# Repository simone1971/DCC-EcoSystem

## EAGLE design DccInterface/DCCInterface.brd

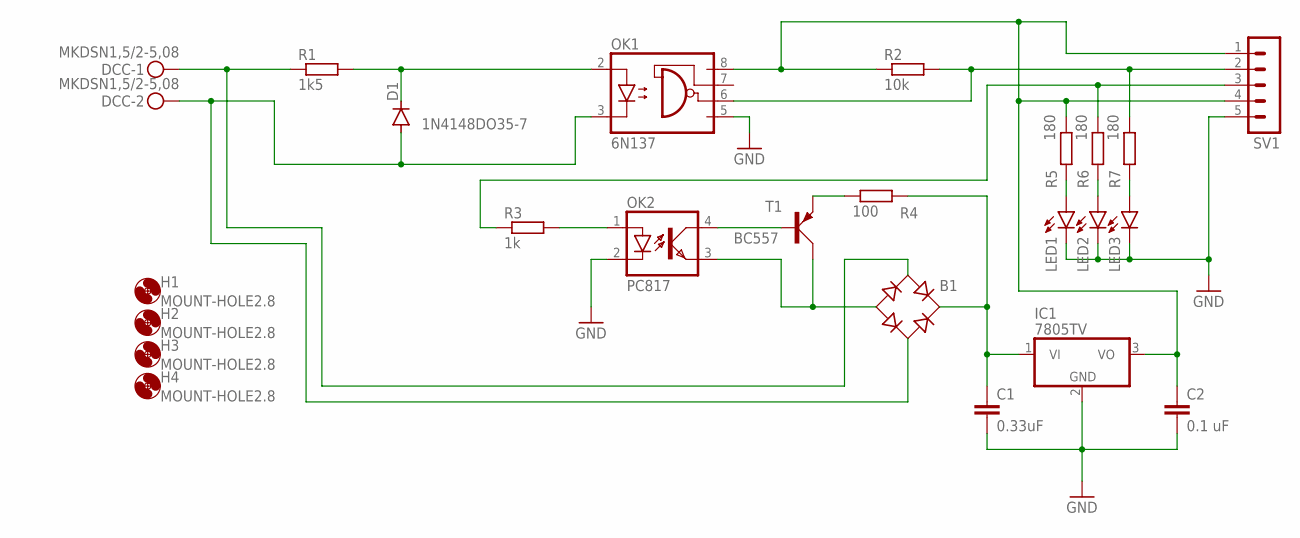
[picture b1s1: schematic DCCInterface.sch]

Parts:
B1: RB1A
C1: 0.33uF; C025-025X050
C2: 0.1 uF; C025-025X050
D1: 1N4148DO35-7; DO35-7
DCC: MKDSN1,5/2-5,08
H1, H2, H3, H4: MOUNT-HOLE2.8; 2,8
IC1: 7805TV; TO220V
LED1, LED2, LED3: LED3MM
OK1: 6N137; DIL08
OK2: PC817; DIL04
R1: 1k5; 0204/7
R2: 10k; 0204/7
R3: 1k; 0204/7
R4: 100; 0204/7
R5, R6, R7: 180; 0204/7
SV1: MA05-1
T1: BC557; SOT54A

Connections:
GND: C1.2, C2.2, IC1.2 (GND), LED1.K (C), LED2.K (C), LED3.K (C), OK1.5 (GND), OK2.2 (C), SV1.5
unnamed: LED1.A, R5.1
unnamed: C2.1, IC1.3 (VO), OK1.8 (VCC), R2.1, R5.2, SV1.1, SV1.4
unnamed: D1.C, OK1.2 (A), R1.2
unnamed: LED2.A, R6.1
unnamed: OK1.6 (VO), R2.2, R7.2, SV1.2
unnamed: B1.AC1, DCC.1, R1.1
unnamed: OK2.1 (A), R3.2
unnamed: OK2.4 (COL), T1.B
unnamed: B1.+, C1.1, IC1.1 (VI), R4.2
unnamed: B1.-, OK2.3 (EMIT), T1.C
unnamed: R4.1, T1.E
unnamed: R3.1, R6.2, SV1.3
unnamed: B1.AC2, D1.A, DCC.2, OK1.3 (C)
unnamed: LED3.A, R7.1

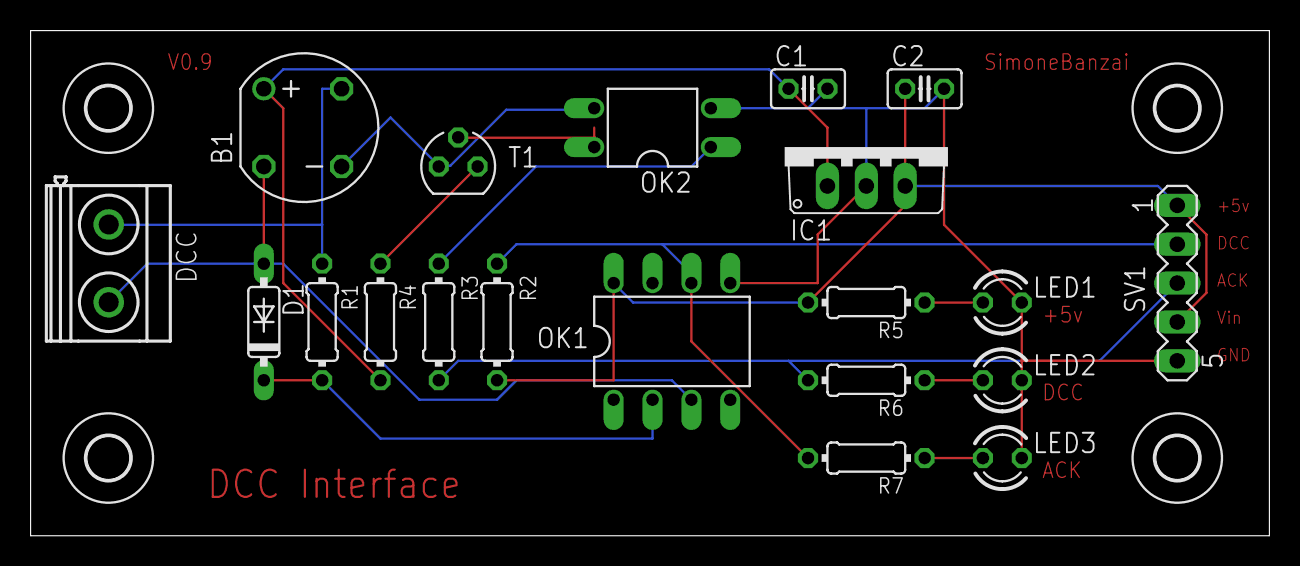
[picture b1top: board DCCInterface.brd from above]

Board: 2 copper layers, 81.0 x 33.0 mm, 24 parts (0 on the bottom side), 15 nets.

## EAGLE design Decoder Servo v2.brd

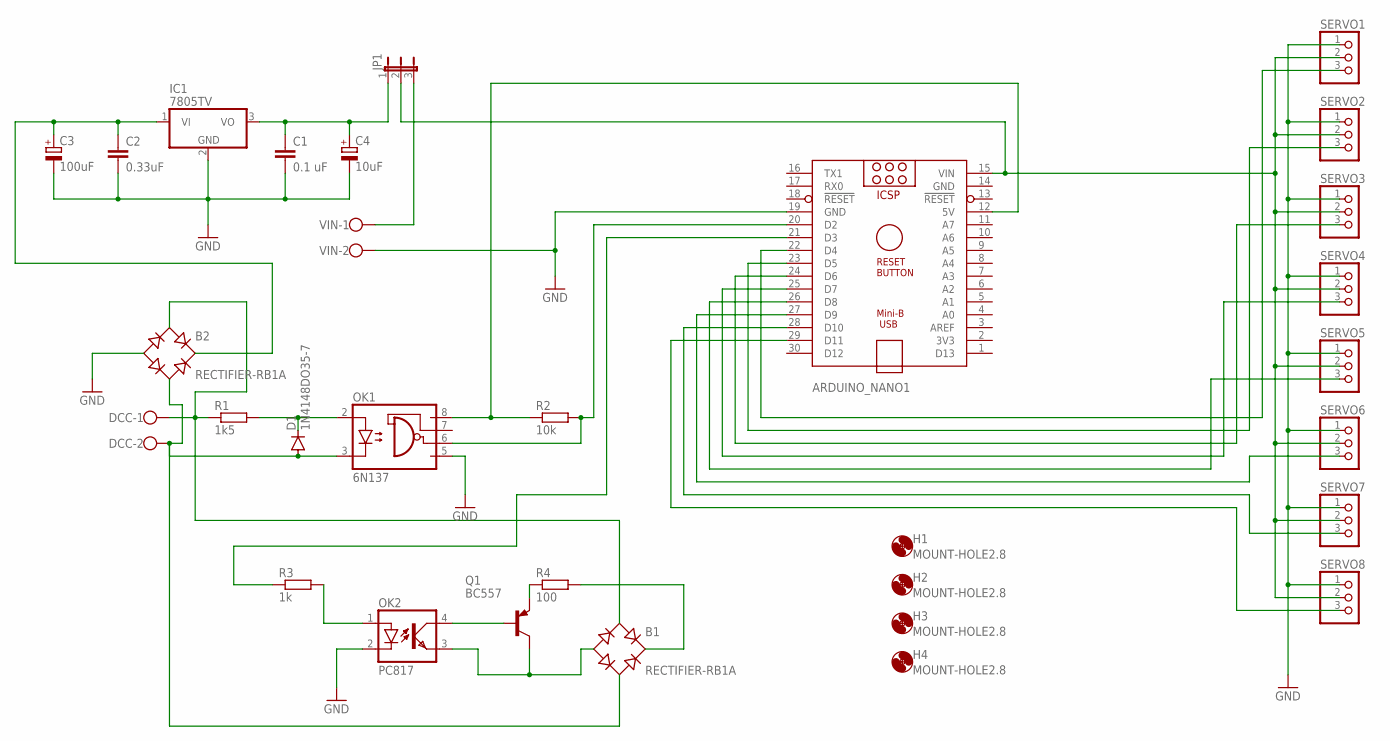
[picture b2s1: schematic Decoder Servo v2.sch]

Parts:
ARDUINO_NANO1: ARDUINO_NANO
B1, B2: RECTIFIER-RB1A; RB1A
C1: 0.1 uF; C025-024X044
C2: 0.33uF; C025-024X044
C3: 100uF; TAP5-50
C4: 10uF; TAP5-50
D1: 1N4148DO35-7; DO35-7
DCC: W237-102
H1, H2, H3, H4: MOUNT-HOLE2.8; 2,8
IC1: 7805TV; TO220V
JP1: JP2E; JP2
OK1: 6N137; DIL08
OK2: PC817; DIL04
Q1: BC557; TO92
R1: 1k5; 0207/10
R2: 10k; 0207/10
R3: 1k; 0207/10
R4: 100; 0207/10
SERVO1, SERVO2, SERVO3, SERVO4, SERVO5, SERVO6, SERVO7, SERVO8: PINHD-1X3; 1X03
VIN: W237-102

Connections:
GND: ARDUINO_NANO1.14 (GND), ARDUINO_NANO1.19 (GND), B2.-, C1.2, C2.2, C3.-, C4.-, IC1.2 (GND), OK1.5 (GND), OK2.2 (C), SERVO1.1, SERVO2.1, SERVO3.1, SERVO4.1, SERVO5.1, SERVO6.1, SERVO7.1, SERVO8.1, VIN.2
unnamed: D1.C, OK1.2 (A), R1.2
unnamed: B1.AC2, B2.AC2, D1.A, DCC.2, OK1.3 (C)
unnamed: ARDUINO_NANO1.12 (5V), OK1.8 (VCC), R2.1
unnamed: ARDUINO_NANO1.20 (D2), OK1.6 (VO), R2.2
unnamed: B1.AC1, B2.AC1, DCC.1, R1.1
unnamed: OK2.4 (COL), Q1.2 (B)
unnamed: ARDUINO_NANO1.21 (D3), R3.1
unnamed: OK2.1 (A), R3.2
unnamed: B1.-, OK2.3 (EMIT), Q1.3 (C)
unnamed: Q1.1 (E), R4.1
unnamed: B1.+, R4.2
unnamed: ARDUINO_NANO1.22 (D4), SERVO1.3
unnamed: B2.+, C2.1, C3.+, IC1.1 (VI)
unnamed: ARDUINO_NANO1.15 (VIN), JP1.2, SERVO1.2, SERVO2.2, SERVO3.2, SERVO4.2, SERVO5.2, SERVO6.2, SERVO7.2, SERVO8.2
unnamed: ARDUINO_NANO1.23 (D5), SERVO2.3
unnamed: ARDUINO_NANO1.24 (D6), SERVO3.3
unnamed: ARDUINO_NANO1.25 (D7), SERVO4.3
unnamed: ARDUINO_NANO1.26 (D8), SERVO5.3
unnamed: ARDUINO_NANO1.27 (D9), SERVO6.3
unnamed: ARDUINO_NANO1.28 (D10), SERVO7.3
unnamed: ARDUINO_NANO1.29 (D11), SERVO8.3
unnamed: C1.1, C4.+, IC1.3 (VO), JP1.1
unnamed: JP1.3, VIN.1

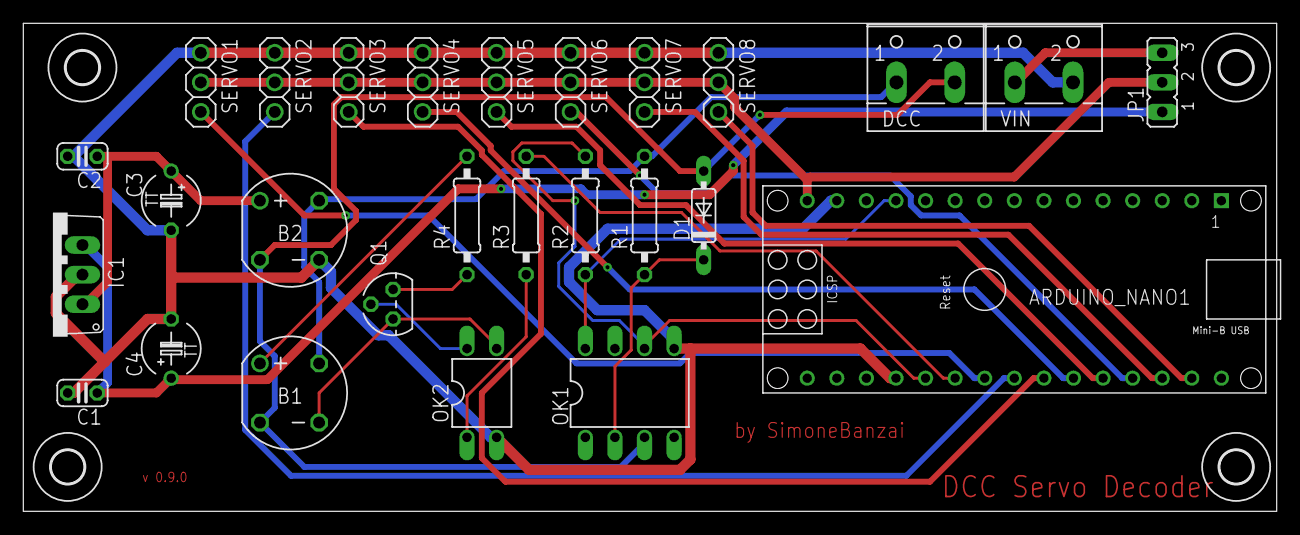
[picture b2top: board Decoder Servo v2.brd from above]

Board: 2 copper layers, 107.6 x 41.9 mm, 31 parts (0 on the bottom side), 24 nets.

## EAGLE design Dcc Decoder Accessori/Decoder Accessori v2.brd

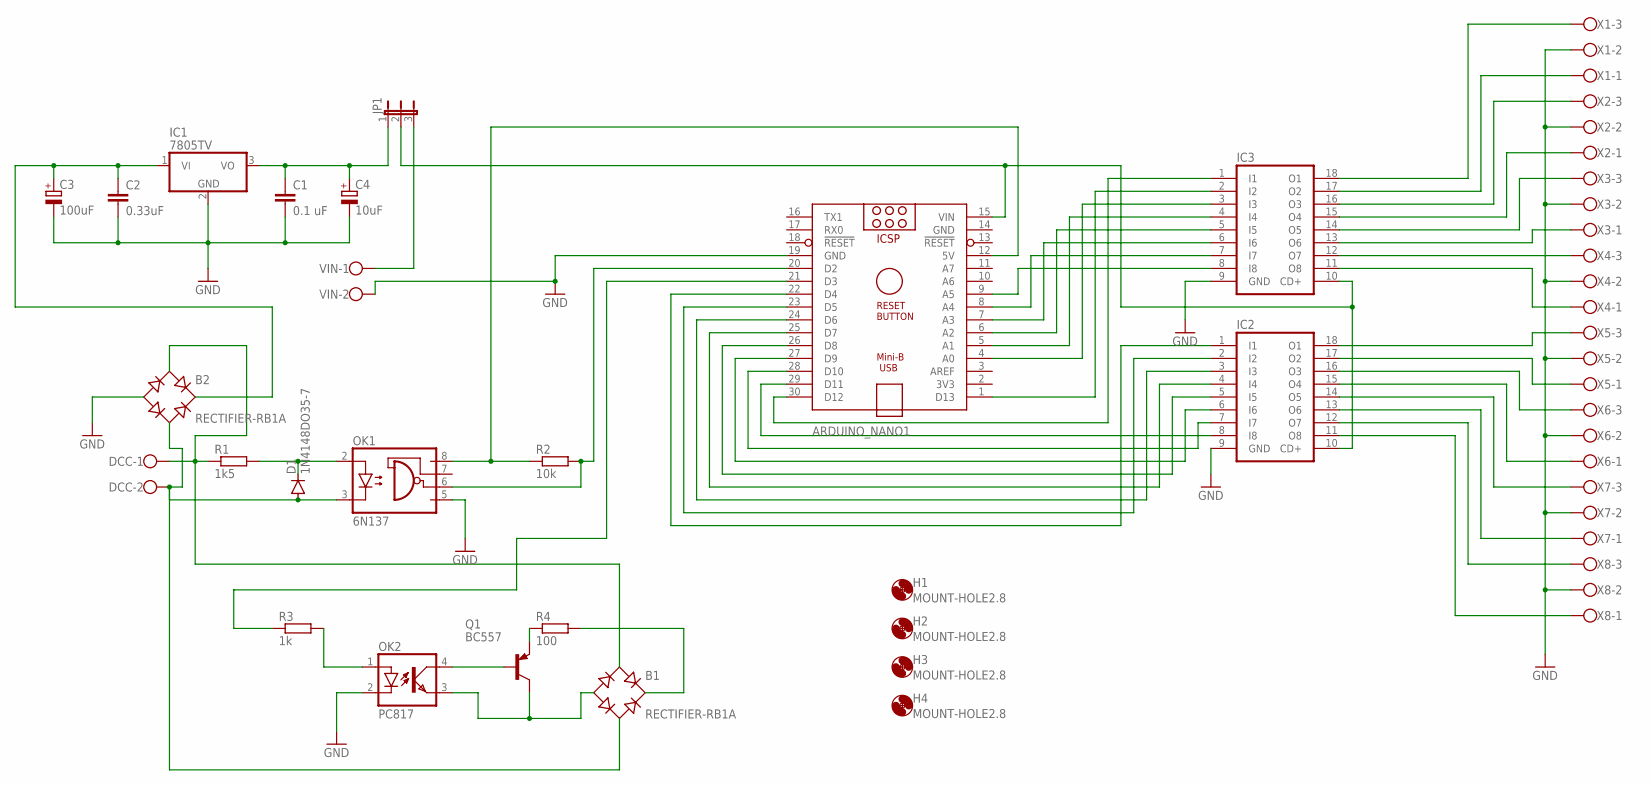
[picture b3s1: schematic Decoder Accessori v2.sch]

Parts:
ARDUINO_NANO1: ARDUINO_NANO
B1, B2: RECTIFIER-RB1A; RB1A
C1: 0.1 uF; C025-024X044
C2: 0.33uF; C025-024X044
C3: 100uF; TAP5-50
C4: 10uF; TAP5-50
D1: 1N4148DO35-7; DO35-7
DCC: W237-102
H1, H2, H3, H4: MOUNT-HOLE2.8; 2,8
IC1: 7805TV; TO220V
IC2, IC3: ULN2803A; DIL18
JP1: JP2E; JP2
OK1: 6N137; DIL08
OK2: PC817; DIL04
Q1: BC557; TO92
R1: 1k5; 0207/10
R2: 10k; 0207/10
R3: 1k; 0207/10
R4: 100; 0207/10
VIN: W237-102
X1, X2, X3, X4, X5, X6, X7, X8: W237-103

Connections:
GND: ARDUINO_NANO1.14 (GND), ARDUINO_NANO1.19 (GND), B2.-, C1.2, C2.2, C3.-, C4.-, IC1.2 (GND), IC2.9 (GND), IC3.9 (GND), OK1.5 (GND), OK2.2 (C), VIN.2, X1.2, X2.2, X3.2, X4.2, X5.2, X6.2, X7.2, X8.2
unnamed: D1.C, OK1.2 (A), R1.2
unnamed: B1.AC2, B2.AC2, D1.A, DCC.2, OK1.3 (C)
unnamed: ARDUINO_NANO1.12 (5V), OK1.8 (VCC), R2.1
unnamed: ARDUINO_NANO1.20 (D2), OK1.6 (VO), R2.2
unnamed: B1.AC1, B2.AC1, DCC.1, R1.1
unnamed: OK2.4 (COL), Q1.2 (B)
unnamed: ARDUINO_NANO1.21 (D3), R3.1
unnamed: OK2.1 (A), R3.2
unnamed: B1.-, OK2.3 (EMIT), Q1.3 (C)
unnamed: Q1.1 (E), R4.1
unnamed: B1.+, R4.2
unnamed: ARDUINO_NANO1.29 (D11), IC2.8 (I8)
unnamed: ARDUINO_NANO1.28 (D10), IC2.7 (I7)
unnamed: B2.+, C2.1, C3.+, IC1.1 (VI)
unnamed: ARDUINO_NANO1.15 (VIN), IC2.10 (CD+), IC3.10 (CD+), JP1.2
unnamed: ARDUINO_NANO1.27 (D9), IC2.6 (I6)
unnamed: ARDUINO_NANO1.26 (D8), IC2.5 (I5)
unnamed: ARDUINO_NANO1.30 (D12), IC3.1 (I1)
unnamed: ARDUINO_NANO1.25 (D7), IC2.4 (I4)
unnamed: ARDUINO_NANO1.24 (D6), IC2.3 (I3)
unnamed: ARDUINO_NANO1.23 (D5), IC2.2 (I2)
unnamed: ARDUINO_NANO1.22 (D4), IC2.1 (I1)
unnamed: ARDUINO_NANO1.1 (D13), IC3.2 (I2)
unnamed: ARDUINO_NANO1.4 (A0), IC3.3 (I3)
unnamed: ARDUINO_NANO1.6 (A2), IC3.5 (I5)
unnamed: ARDUINO_NANO1.5 (A1), IC3.4 (I4)
unnamed: ARDUINO_NANO1.7 (A3), IC3.6 (I6)
unnamed: ARDUINO_NANO1.8 (A4), IC3.7 (I7)
unnamed: IC3.11 (O8), X4.1
unnamed: ARDUINO_NANO1.9 (A5), IC3.8 (I8)
unnamed: IC3.12 (O7), X4.3
unnamed: IC3.13 (O6), X3.1
unnamed: IC3.14 (O5), X3.3
unnamed: IC3.15 (O4), X2.1
unnamed: IC3.16 (O3), X2.3
unnamed: IC3.17 (O2), X1.1
unnamed: IC3.18 (O1), X1.3
unnamed: IC2.18 (O1), X5.3
unnamed: IC2.17 (O2), X5.1
unnamed: IC2.16 (O3), X6.3
unnamed: IC2.15 (O4), X6.1
unnamed: IC2.14 (O5), X7.3
unnamed: IC2.13 (O6), X7.1
unnamed: IC2.12 (O7), X8.3
unnamed: IC2.11 (O8), X8.1
unnamed: C1.1, C4.+, IC1.3 (VO), JP1.1
unnamed: JP1.3, VIN.1

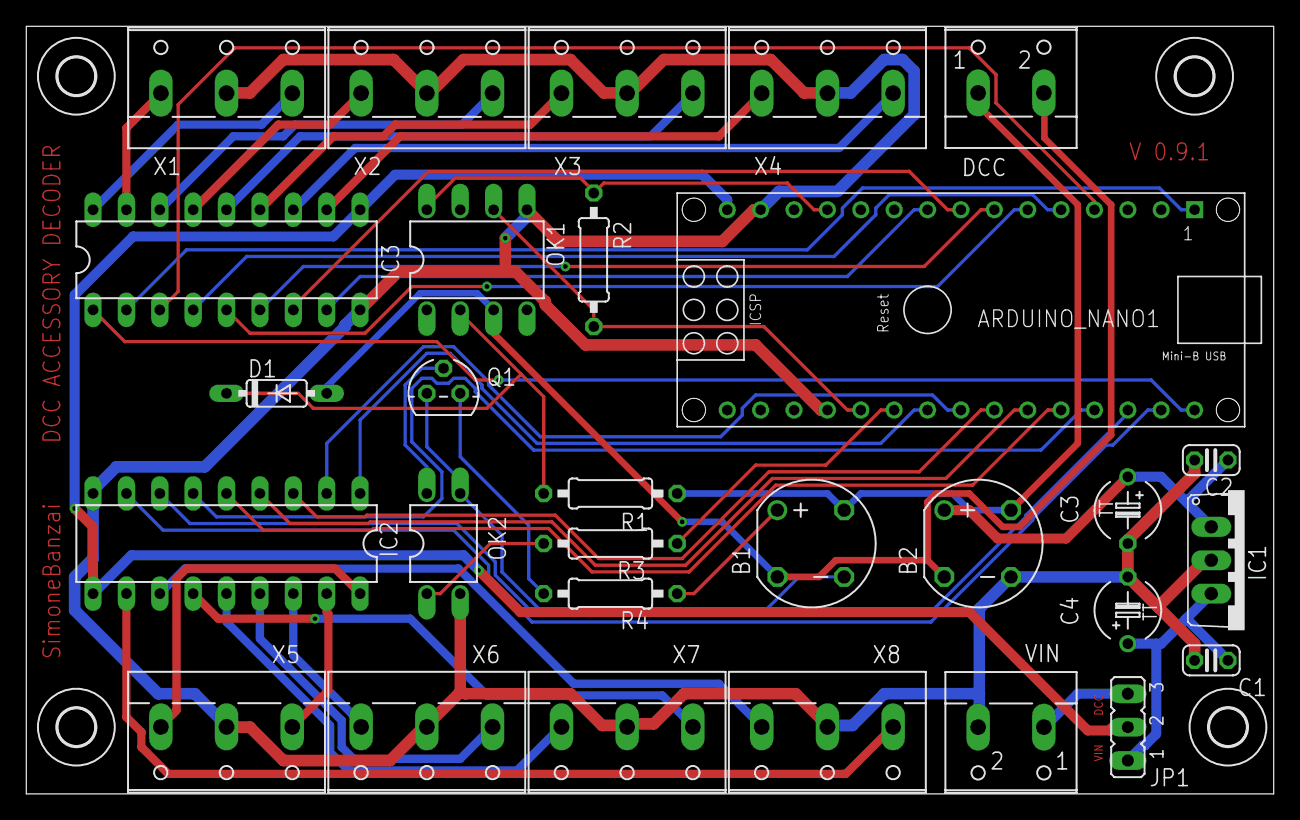
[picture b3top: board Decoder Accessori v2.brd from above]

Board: 2 copper layers, 94.9 x 58.4 mm, 33 parts (0 on the bottom side), 48 nets.

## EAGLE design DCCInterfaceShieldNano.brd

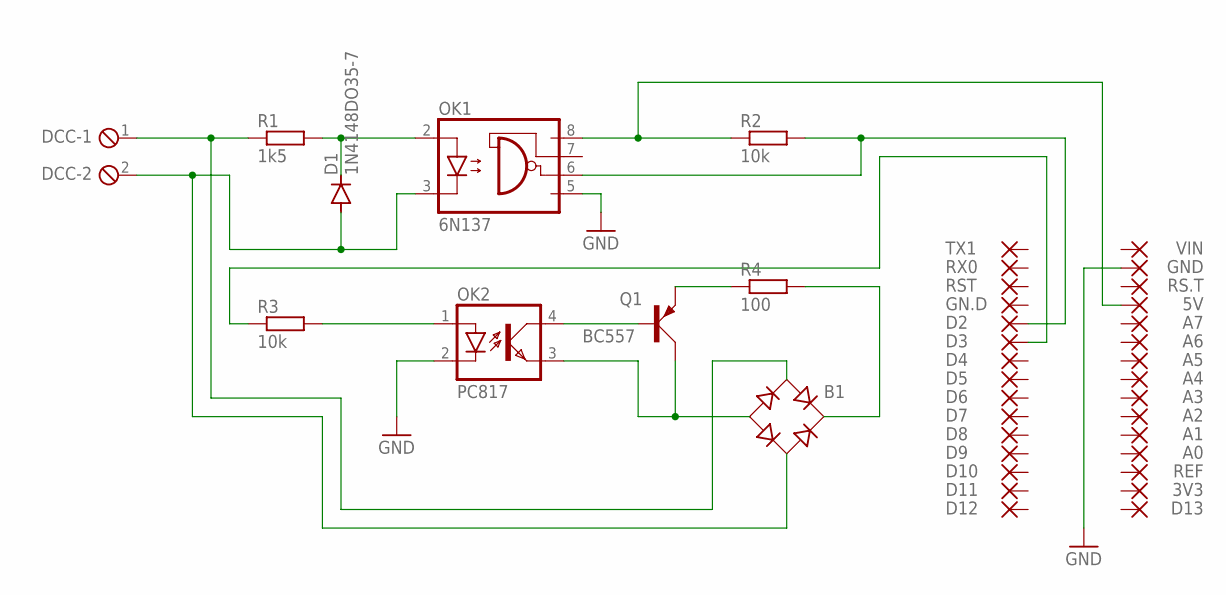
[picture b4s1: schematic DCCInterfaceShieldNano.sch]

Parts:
3V3, 5V: 1,6/0,8
A0, A1, A2, A3, A4, A5, A6, A7: 1,6/0,8
B1: RB1A
D1: 1N4148DO35-7; DO35-7
D2, D3, D4, D5, D6, D7, D8, D9, D10, D11, D12, D13: 1,6/0,8
DCC: MPT2; 2POL254
GN.D: 1,6/0,8
GND: 1,6/0,8
OK1: 6N137; DIL08
OK2: PC817; DIL04
Q1: BC557; SOT54A
R1: 1k5; 0204V
R2, R3: 10k; 0204V
R4: 100; 0204V
REF: 1,6/0,8
RS.T: 1,6/0,8
RST: 1,6/0,8
RX0: 1,6/0,8
TX1: 1,6/0,8
VIN: 1,6/0,8

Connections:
GND: GND.1, OK1.5 (GND), OK2.2 (C)
unnamed: 5V.1, OK1.8 (VCC), R2.1
unnamed: D1.C, OK1.2 (A), R1.2
unnamed: D2.1, OK1.6 (VO), R2.2
unnamed: B1.AC1, DCC.1, R1.1
unnamed: OK2.1 (A), R3.2
unnamed: OK2.4 (COL), Q1.B
unnamed: B1.+, R4.2
unnamed: B1.-, OK2.3 (EMIT), Q1.C
unnamed: Q1.E, R4.1
unnamed: D3.1, R3.1
unnamed: B1.AC2, D1.A, DCC.2, OK1.3 (C)

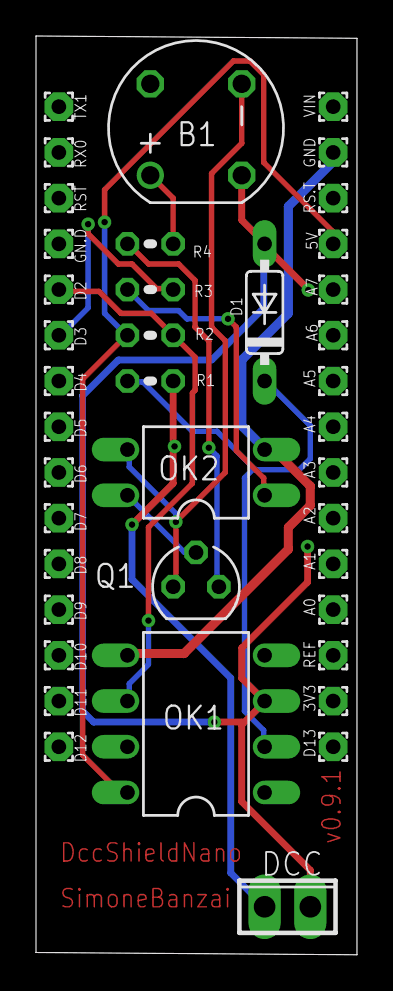
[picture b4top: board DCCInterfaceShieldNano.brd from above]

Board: 2 copper layers, 17.8 x 51.0 mm, 40 parts (0 on the bottom side), 12 nets.

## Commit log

2022-04-19 Organizzazione in cartelle per le varie schede
